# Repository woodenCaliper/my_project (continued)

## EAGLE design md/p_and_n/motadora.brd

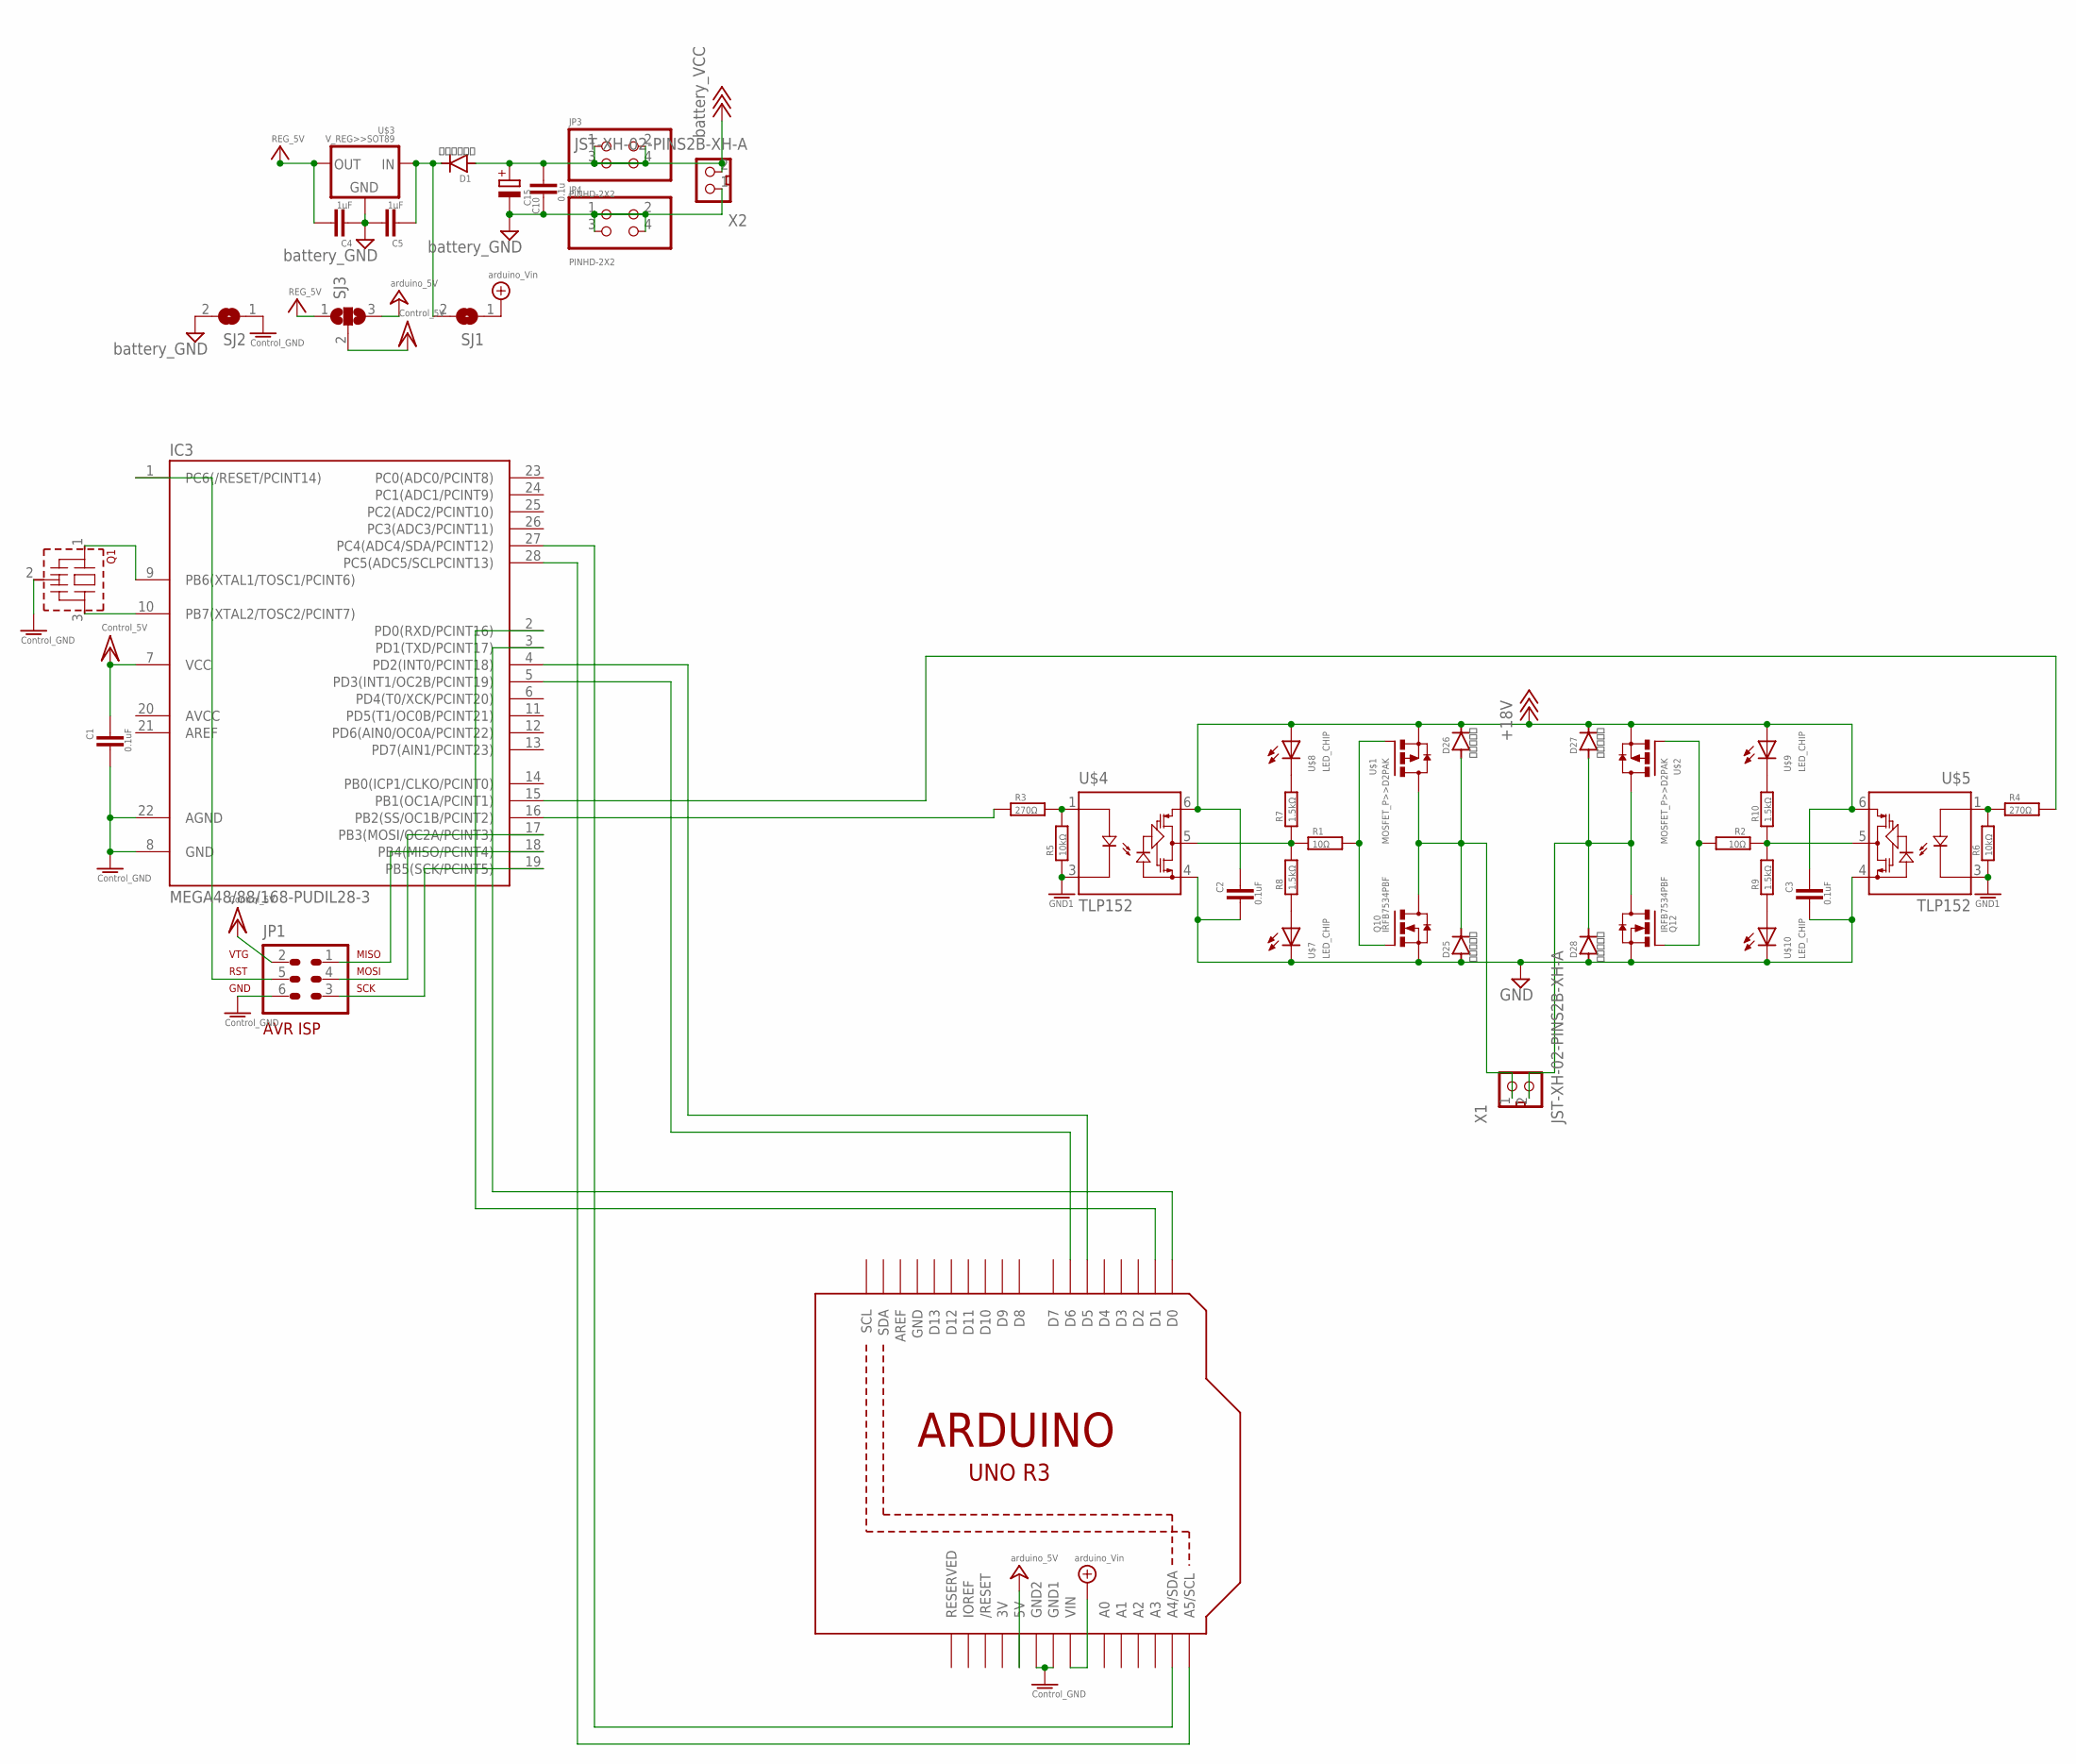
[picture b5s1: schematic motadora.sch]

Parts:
C1, C2, C3: 0.1uF; 2012
C4, C5: 1μF; C2012
C10: 0.1u; C025-025X050
C15: CPOL-EUTT2D5L; TT2D5L
D1: ＳＤ１０３Ａ; D-7.5
D25, D26, D27, D28: ＭＳ１８Ｆ; MS18F
IC3: MEGA48/88/168-PUDIL28-3; DIL28-3
JP1: AVR-ISP-6
JP3, JP4: PINHD-2X2; 2X02
Q1: CSTLS_G; CSTLS_G8
Q10, Q12: IRFB7534PBF; D2PACK
R1, R2: 10Ω; 2012
R3, R4: 270Ω; 2012
R5, R6: 10kΩ; 2012
R7, R8, R9, R10: 1.5kΩ; 2012
SJ1, SJ2: SJ
SJ3: SJ2W; SJ_2
U1: ARDUINOR3-BPLACE
U$1, U$2: MOSFET_P>>D2PAK; D2PAK
U$3: V_REG>>SOT89; SOT89
U$4, U$5: TLP152; 11-4L1S
U$7, U$8, U$9, U$10: LED_CHIP; 2012
X1, X2: JST-XH-02-PINS2B-XH-A; S2B-XH-A

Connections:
3V: U1.3V
+5V: C4.1, SJ3.1, U$3.1 (OUT)
+18V: C2.2, C3.2, C10.1, C15.+, D1.A, D26.P$2 (C), D27.P$2 (C), JP3.1, JP3.2, JP3.3, JP3.4, U$1.3 (S), U$2.3 (S), U$4.6, U$5.6, U$8.P$1 (A), U$9.P$1 (A), X2.2
GND: C2.1, C3.1, C4.2, C5.1, C10.2, C15.-, D25.P$1 (A), D28.P$1 (A), JP4.1, JP4.2, JP4.3, JP4.4, Q10.3 (S), Q12.3 (S), SJ2.2, U1.GND, U$3.2 (GND), U$3.2.1 (GND), U$4.4, U$5.4, U$7.P$2 (C), U$10.P$2 (C), X2.1
GND1: C1.1, IC3.8 (GND), IC3.22 (AGND), JP1.6, Q1.2 (VSS), R5.1, R6.1, SJ2.1, U1.GND1, U1.GND2, U$4.3, U$5.3
unnamed: R2.1, R9.2, R10.1, U$5.5
unnamed: Q12.1 (G), R2.2, U$2.1 (G)
unnamed: IC3.28 (PC5(ADC5/SCLPCINT13)), U1.A5 (A5/SCL)
unnamed: R3.2, R5.2, U$4.1
unnamed: R1.1, R7.1, R8.2, U$4.5
unnamed: R4.1, R6.2, U$5.1
unnamed: IC3.17 (PB3(MOSI/OC2A/PCINT3)), JP1.4
unnamed: IC3.27 (PC4(ADC4/SDA/PCINT12)), U1.A4 (A4/SDA)
unnamed: IC3.10 (PB7(XTAL2/TOSC2/PCINT7)), Q1.3
unnamed: IC3.3 (PD1(TXD/PCINT17)), U1.D0
unnamed: IC3.2 (PD0(RXD/PCINT16)), U1.D1
unnamed: C5.2, D1.C, SJ1.2, U$3.3 (IN)
unnamed: D25.P$2 (C), D26.P$1 (A), Q10.2 (D), U$1.4 (D), X1.1
unnamed: R7.2, U$8.P$2 (C)
unnamed: IC3.9 (PB6(XTAL1/TOSC1/PCINT6)), Q1.1
unnamed: R8.1, U$7.P$1 (A)
unnamed: IC3.1 (PC6(/RESET/PCINT14)), JP1.5
unnamed: Q10.1 (G), R1.2, U$1.1 (G)
unnamed: R9.1, U$10.P$1 (A)
unnamed: R10.2, U$9.P$2 (C)
unnamed: D27.P$1 (A), D28.P$2 (C), Q12.2 (D), U$2.4 (D), X1.2
unnamed: IC3.19 (PB5(SCK/PCINT5)), JP1.3
unnamed: IC3.4 (PD2(INT0/PCINT18)), U1.D5
unnamed: IC3.5 (PD3(INT1/OC2B/PCINT19)), U1.D6
unnamed: IC3.18 (PB4(MISO/PCINT4)), JP1.1
unnamed: IC3.16 (PB2(SS/OC1B/PCINT2)), R3.1
unnamed: IC3.15 (PB1(OC1A/PCINT1)), R4.2
VCC5: SJ3.3, U1.5V
VCC6: SJ1.1, U1.VIN
VCC7: C1.2, IC3.7 (VCC), JP1.2, SJ3.2

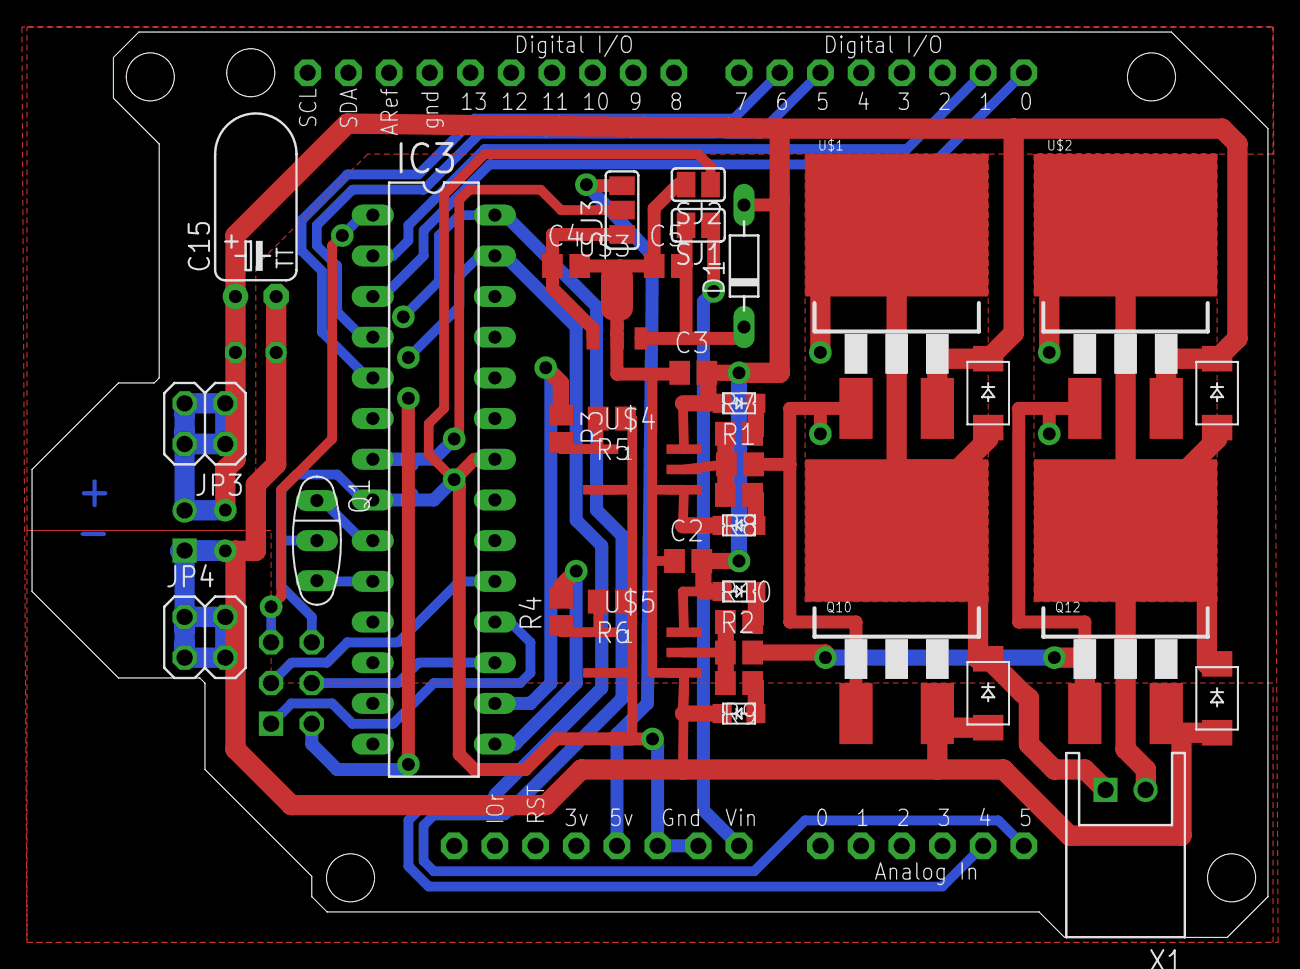
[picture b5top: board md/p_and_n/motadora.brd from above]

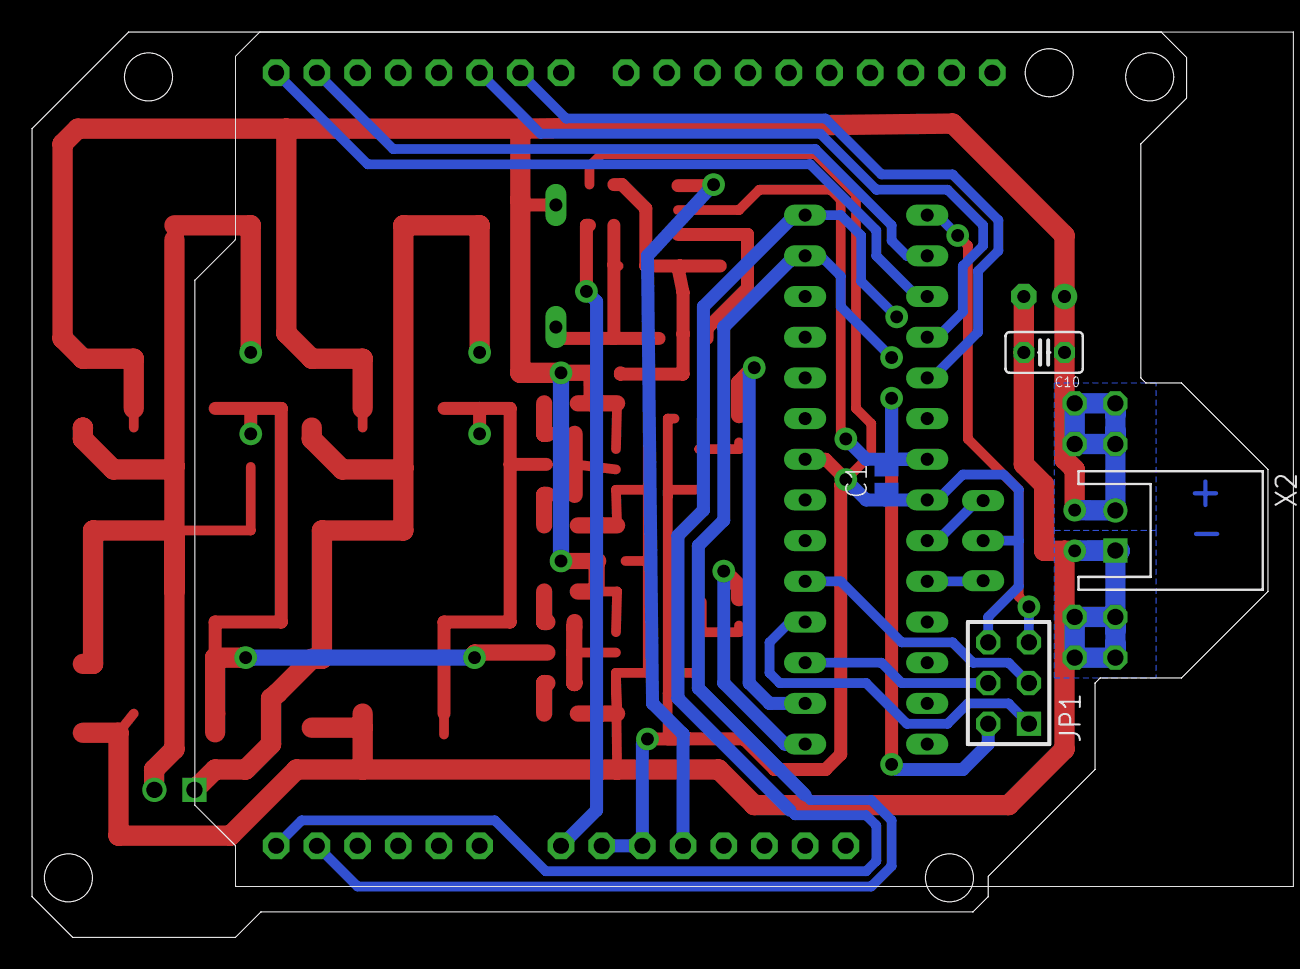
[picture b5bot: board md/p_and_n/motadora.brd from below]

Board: 2 copper layers, 77.2 x 56.5 mm, 44 parts (4 on the bottom side), 34 nets.

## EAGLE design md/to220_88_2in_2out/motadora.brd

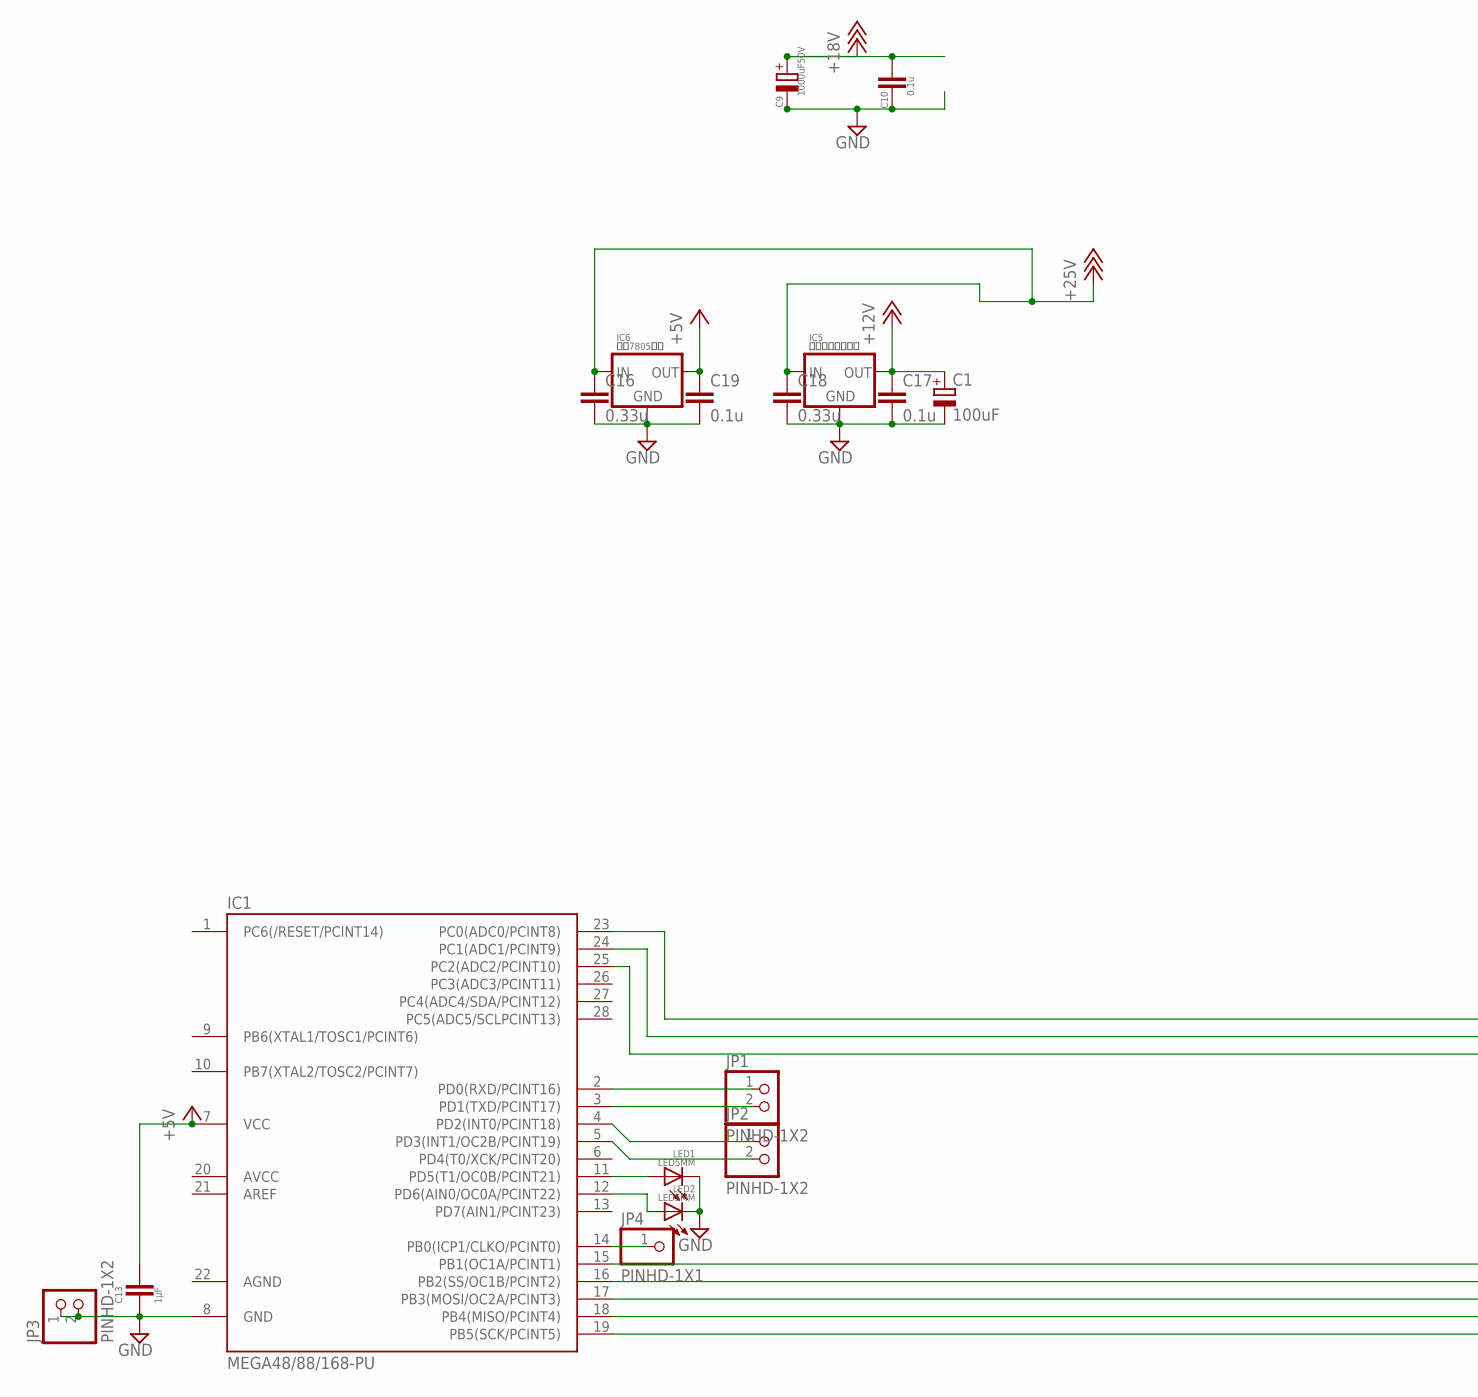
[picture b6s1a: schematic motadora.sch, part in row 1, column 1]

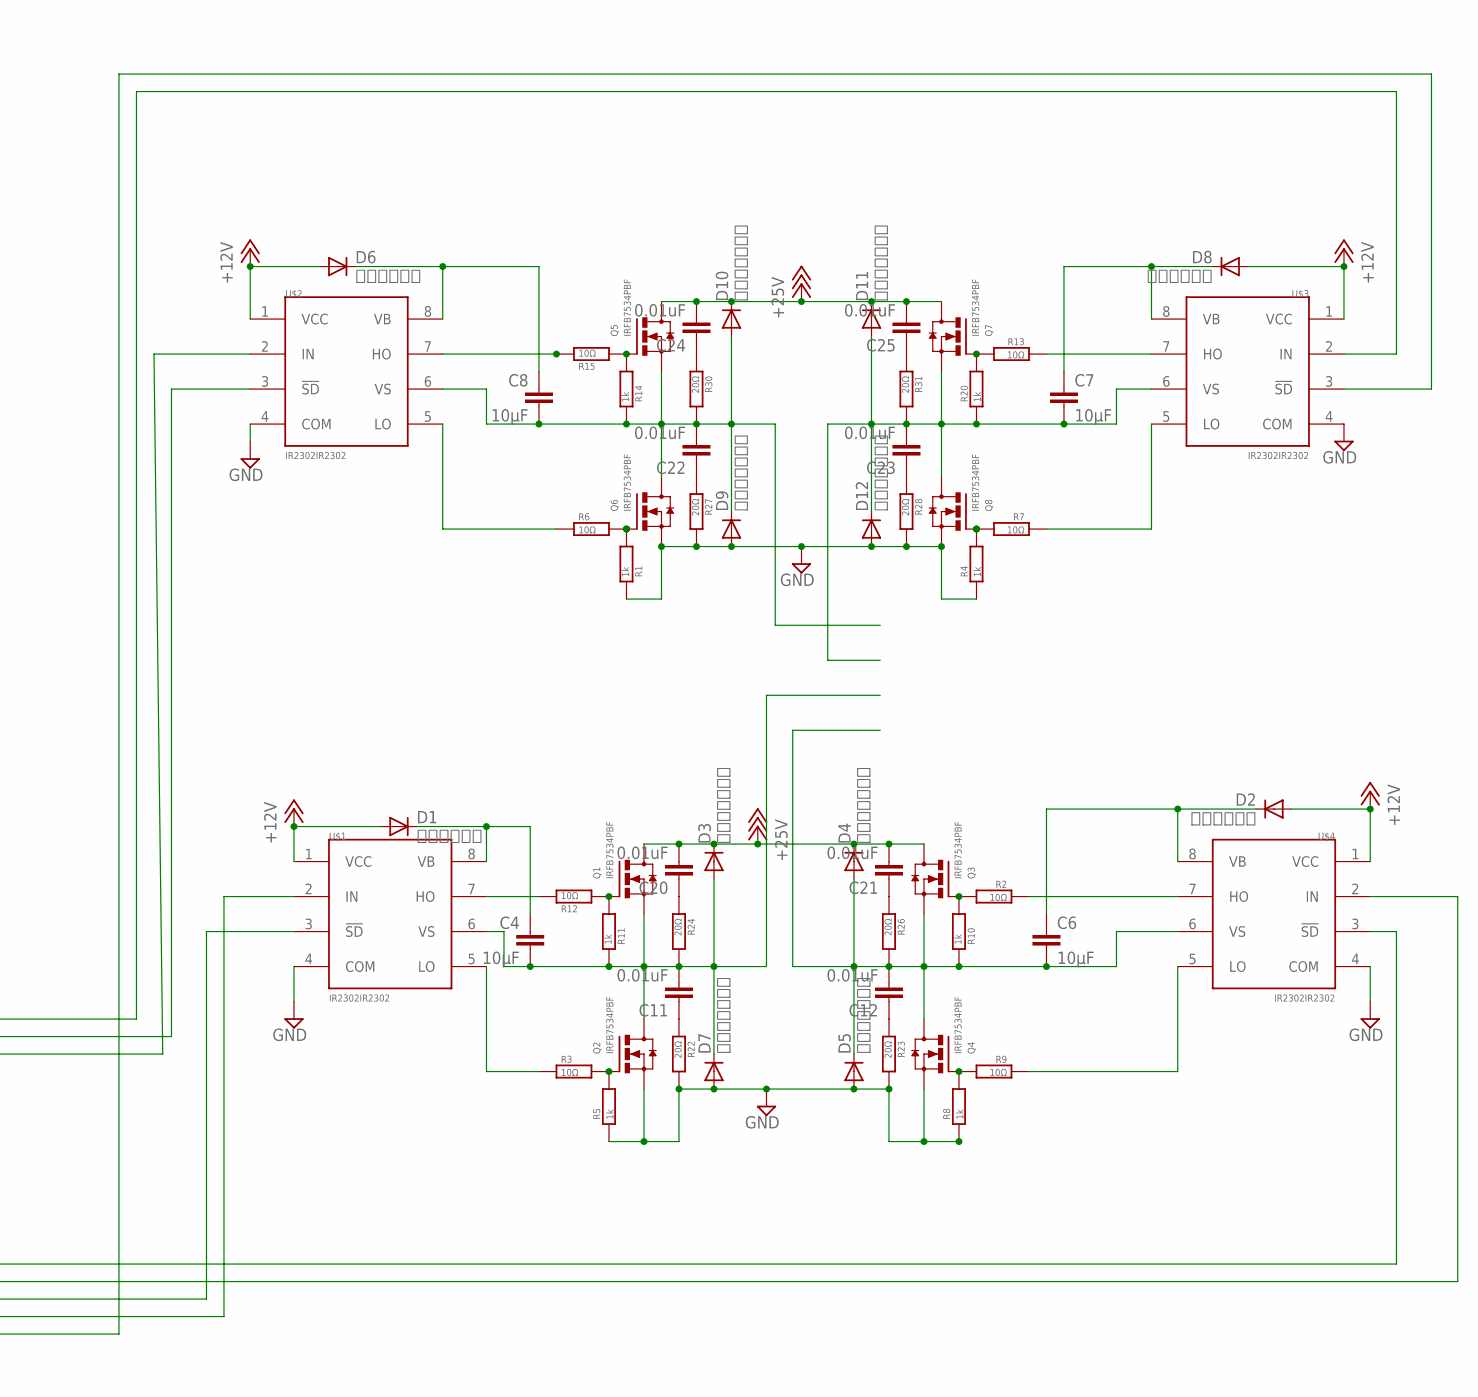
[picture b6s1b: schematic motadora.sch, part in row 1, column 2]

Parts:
C1: 100uF; TT2D6
C4, C6, C7, C8: 10μF; C025-025X050
C9: 1000uF50V; E2,5-7
C10, C17, C19: 0.1u; C025-025X050
C11, C12, C20, C21, C22, C23, C24, C25: 0.01uF; C025-024X044
C13: 1μF; C025-025X050
C16, C18: 0.33u; C025-025X050
D1, D2, D6, D8: ＳＤ１０３Ａ; D-5
D3, D4, D5, D7, D9, D10, D11, D12: １１ＥＱＳ０６; D-5
IC1: MEGA48/88/168-PU; DIL28-3
IC5: ＬＭ７８１２ＣＶ; TO-92
IC6: ＬＭ7805ＣＶ; TO-92
JP1, JP2, JP3: PINHD-1X2; 1X02
JP4: PINHD-1X1; 1X01
LED1, LED2: LED5MM
Q1, Q2, Q3, Q4, Q5, Q6, Q7, Q8: IRFB7534PBF; TO220_2
R1, R4, R5, R8, R10, R11, R14, R20: 1k; 1/4W(8MM)
R2, R3, R6, R7, R9, R12, R13, R15: 10Ω; 1/4W(2.5MM)_
R22, R23, R24, R26, R27, R28, R30, R31: 20Ω; 1/4W(2.5MM)_
U$1, U$2, U$3, U$4: IR2302IR2302; DIL08

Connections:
+5V: C13.1, C19.1, IC1.7 (VCC), IC6.1 (OUT)
+12V: C1.+, C17.1, D1.A, D2.A, D6.A, D8.A, IC5.1 (OUT), U$1.1 (VCC), U$2.1 (VCC), U$3.1 (VCC), U$4.1 (VCC)
+18V: C9.+, C10.1, C16.1, C18.1, C20.2, C21.2, C24.2, C25.2, D3.C, D4.C, D10.C, D11.C, IC5.3 (IN), IC6.3 (IN), Q1.2 (D), Q3.2 (D), Q5.2 (D), Q7.2 (D)
AGND: IC1.22 (AGND)
GND: C1.-, C9.-, C10.2, C13.2, C16.2, C17.2, C18.2, C19.2, D5.A, D7.A, D9.A, D12.A, IC1.8 (GND), IC5.2 (GND), IC6.2 (GND), JP3.1, JP3.2, LED1.K (C), LED2.K (C), Q2.3 (S), Q4.3 (S), Q6.3 (S), Q8.3 (S), R1.1, R4.1, R5.1, R8.1, R22.4 (2), R23.4 (2), R27.4 (2), R28.4 (2), U$1.4 (COM), U$2.4 (COM), U$3.4 (COM), U$4.4 (COM)
unnamed: R15.3 (1), U$2.7 (HO)
unnamed: R13.3 (1), U$3.7 (HO)
unnamed: R12.3 (1), U$1.7 (HO)
unnamed: Q2.1 (G), R3.4 (2), R5.2
unnamed: R2.3 (1), U$4.7 (HO)
unnamed: R6.3 (1), U$2.5 (LO)
unnamed: Q1.1 (G), R11.2, R12.4 (2)
unnamed: C4.2, C11.2, D3.A, D7.C, Q1.3 (S), Q2.2 (D), R11.1, R24.4 (2), U$1.6 (VS)
unnamed: C4.1, D1.C, U$1.8 (VB)
unnamed: C6.1, D2.C, U$4.8 (VB)
unnamed: R3.3 (1), U$1.5 (LO)
unnamed: C7.1, D8.C, U$3.8 (VB)
unnamed: Q5.1 (G), R14.2, R15.4 (2)
unnamed: C6.2, C12.2, D4.A, D5.C, Q3.3 (S), Q4.2 (D), R10.1, R26.4 (2), U$4.6 (VS)
unnamed: C8.1, D6.C, U$2.8 (VB)
unnamed: Q4.1 (G), R8.2, R9.4 (2)
unnamed: IC1.11 (PD5(T1/OC0B/PCINT21)), LED1.A
unnamed: C7.2, C23.2, D11.A, D12.C, Q7.3 (S), Q8.2 (D), R20.1, R31.4 (2), U$3.6 (VS)
unnamed: IC1.17 (PB3(MOSI/OC2A/PCINT3)), U$1.3 (!SD)
unnamed: Q6.1 (G), R1.2, R6.4 (2)
unnamed: IC1.15 (PB1(OC1A/PCINT1)), U$4.3 (!SD)
unnamed: IC1.12 (PD6(AIN0/OC0A/PCINT22)), LED2.A
unnamed: IC1.24 (PC1(ADC1/PCINT9)), U$2.3 (!SD)
unnamed: IC1.2 (PD0(RXD/PCINT16)), JP1.1
unnamed: Q8.1 (G), R4.2, R7.4 (2)
unnamed: C8.2, C22.2, D9.C, D10.A, Q5.3 (S), Q6.2 (D), R14.1, R30.4 (2), U$2.6 (VS)
unnamed: IC1.16 (PB2(SS/OC1B/PCINT2)), U$4.2 (IN)
unnamed: IC1.3 (PD1(TXD/PCINT17)), JP1.2
unnamed: IC1.4 (PD2(INT0/PCINT18)), JP2.1
unnamed: C12.1, R23.3 (1)
unnamed: IC1.5 (PD3(INT1/OC2B/PCINT19)), JP2.2
unnamed: C11.1, R22.3 (1)
unnamed: Q3.1 (G), R2.4 (2), R10.2
unnamed: R7.3 (1), U$3.5 (LO)
unnamed: IC1.23 (PC0(ADC0/PCINT8)), U$3.2 (IN)
unnamed: C20.1, R24.3 (1)
unnamed: C21.1, R26.3 (1)
unnamed: C22.1, R27.3 (1)
unnamed: C23.1, R28.3 (1)
unnamed: C24.1, R30.3 (1)
unnamed: C25.1, R31.3 (1)
unnamed: IC1.19 (PB5(SCK/PCINT5)), U$3.3 (!SD)
unnamed: IC1.18 (PB4(MISO/PCINT4)), U$1.2 (IN)
unnamed: Q7.1 (G), R13.4 (2), R20.2
unnamed: IC1.25 (PC2(ADC2/PCINT10)), U$2.2 (IN)
unnamed: IC1.14 (PB0(ICP1/CLKO/PCINT0)), JP4.1
unnamed: R9.3 (1), U$4.5 (LO)

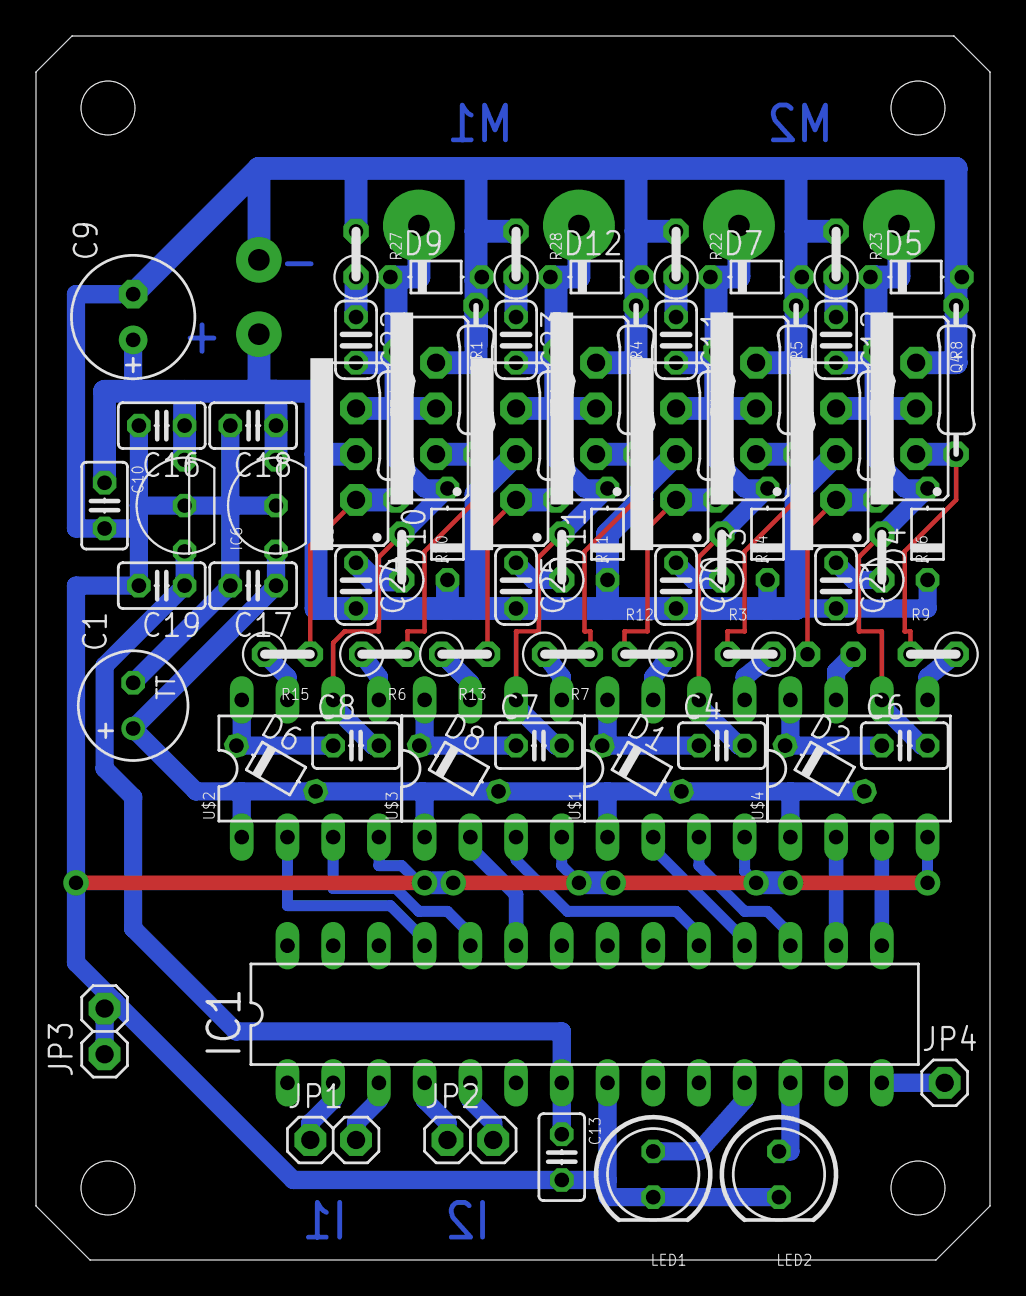
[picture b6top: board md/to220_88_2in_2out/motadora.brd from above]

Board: 2 copper layers, 53.0 x 68.0 mm, 77 parts (1 on the bottom side), 51 nets.

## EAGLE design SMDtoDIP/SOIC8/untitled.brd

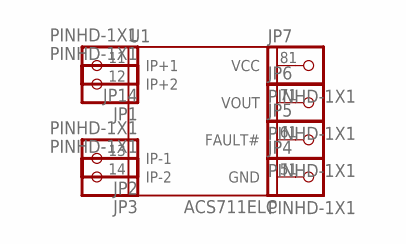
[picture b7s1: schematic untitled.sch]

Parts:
JP1, JP2, JP3, JP4, JP5, JP6, JP7, JP14: PINHD-1X1; 1X01
U1: ACS711ELC; SOIC8

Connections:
unnamed: JP14.1, U1.1 (IP+1)
unnamed: JP1.1, U1.2 (IP+2)
unnamed: JP2.1, U1.3 (IP-1)
unnamed: JP3.1, U1.4 (IP-2)
unnamed: JP4.1, U1.5 (GND)
unnamed: JP5.1, U1.6 (FAULT#)
unnamed: JP6.1, U1.7 (VOUT)
unnamed: JP7.1, U1.8 (VCC)

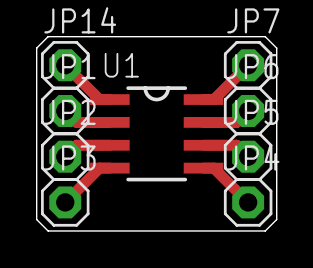
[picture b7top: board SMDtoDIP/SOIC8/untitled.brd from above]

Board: 2 copper layers, 13.3 x 10.8 mm, 9 parts (0 on the bottom side), 8 nets.

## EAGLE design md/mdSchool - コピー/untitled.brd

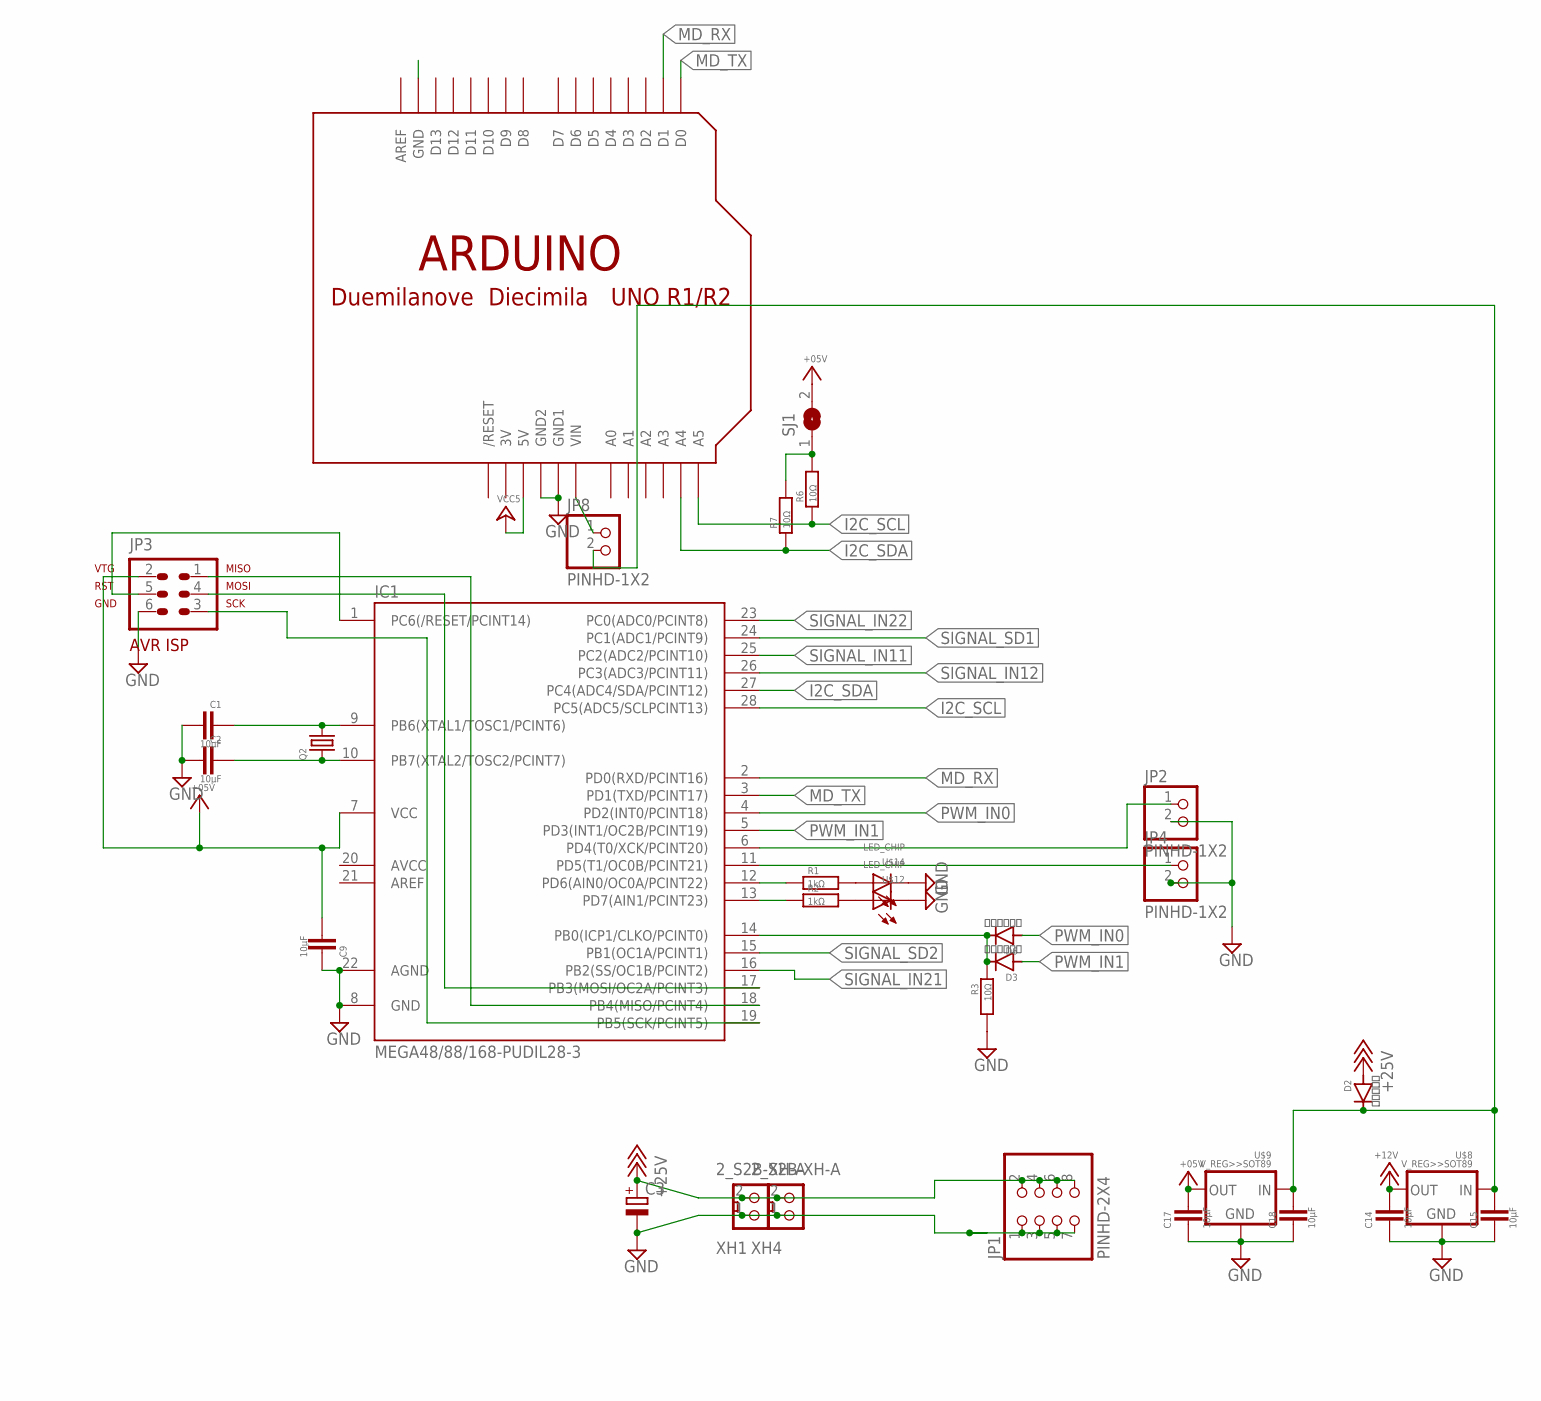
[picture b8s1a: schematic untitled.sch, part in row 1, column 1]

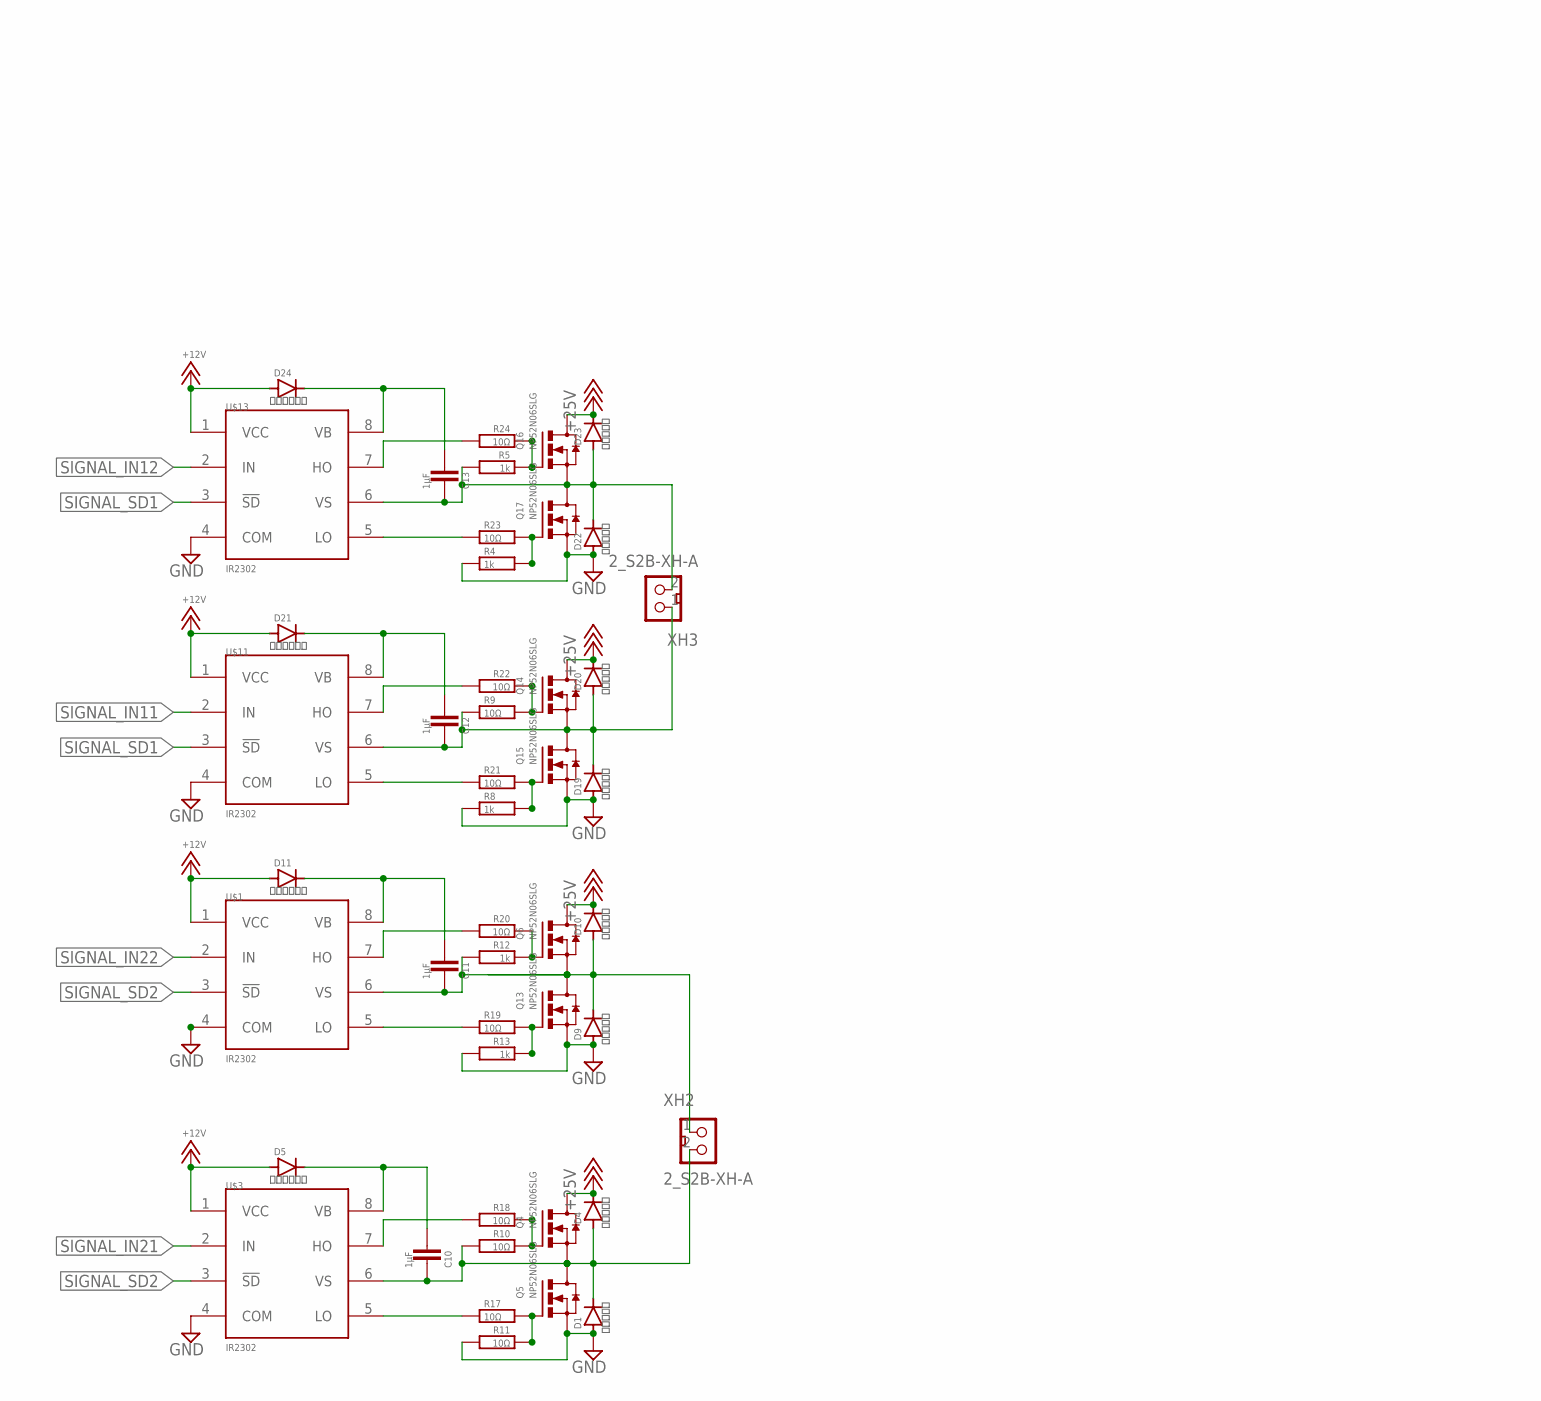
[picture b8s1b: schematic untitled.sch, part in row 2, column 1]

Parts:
C1, C2, C9, C14, C15, C17, C18: 10μF; 2012
C3: CPOL-EUUD-6,3X8,8; UD-6,3X5,8_NICHICON
C10, C11, C12, C13: 1μF; 2012
D1, D2, D4, D9, D10, D19, D20, D22, D23: ＭＳ１８Ｆ; MS18F
D3, D5, D6, D11, D21, D24: ＳＤ１０３Ａ; SOD123
IC1: MEGA48/88/168-PUDIL28-3; DIL28-3
JP1: PINHD-2X4; 2X04
JP2, JP4, JP8: PINHD-1X2; 1X02
JP3: AVR-ISP-6
Q2: CRYSTALHC49UP; HC49UP
Q4, Q5, Q6, Q13, Q14, Q15, Q16, Q17: NP52N06SLG; TO252
R1, R2: 1kΩ; 2012
R3, R6, R7, R9, R10, R11, R17, R18, R19, R20, R21, R22, R23, R24: 10Ω; 2012
R4, R5, R8, R12, R13: 1k; 2012
SJ1: SJ
U$1, U$3, U$11, U$13: IR2302; DIL08
U$2: ARDUINO-NOHOLE
U$8, U$9: V_REG>>SOT89; SOT89
U$12, U$14: LED_CHIP; 2012
XH1, XH2, XH3, XH4: 2_S2B-XH-A; S2B-XH-A

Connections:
3V: U$2.3V
+5V: C9.1, C17.1, IC1.7 (VCC), JP3.2, SJ1.2, U$9.1 (OUT)
+12V: C14.1, D5.A, D11.A, D21.A, D24.A, U$1.1 (VCC), U$3.1 (VCC), U$8.1 (OUT), U$11.1 (VCC), U$13.1 (VCC)
+18V: C3.+, D2.P$1 (A), D4.P$2 (C), D10.P$2 (C), D20.P$2 (C), D23.P$2 (C), JP1.2, JP1.4, JP1.6, JP1.8, Q4.3 (D), Q6.3 (D), Q14.3 (D), Q16.3 (D), XH1.2, XH4.2
GND: C1.1, C2.1, C3.-, C9.2, C14.2, C15.2, C17.2, C18.2, D1.P$1 (A), D9.P$1 (A), D19.P$1 (A), D22.P$1 (A), IC1.8 (GND), IC1.22 (AGND), JP1.1, JP1.3, JP1.5, JP1.7, JP2.2, JP3.6, JP4.2, Q5.2 (S), Q13.2 (S), Q15.2 (S), Q17.2 (S), R3.2, R4.1, R8.1, R11.2, R13.2, U$1.4 (COM), U$2.GND1, U$2.GND2, U$3.4 (COM), U$8.2 (GND), U$8.2.1 (GND), U$9.2 (GND), U$9.2.1 (GND), U$11.4 (COM), U$12.P$2 (C), U$13.4 (COM), U$14.P$2 (C), XH1.1, XH4.1
I2C_SCL: IC1.28 (PC5(ADC5/SCLPCINT13)), R6.1, U$2.A5
I2C_SDA: IC1.27 (PC4(ADC4/SDA/PCINT12)), R7.1, U$2.A4
MD_RX: IC1.2 (PD0(RXD/PCINT16)), U$2.D1
MD_TX: IC1.3 (PD1(TXD/PCINT17)), U$2.D0
unnamed: C15.1, C18.1, D2.P$2 (C), JP8.2, U$8.3 (IN), U$9.3 (IN)
unnamed: JP8.1, U$2.VIN
unnamed: C13.2, D22.P$2 (C), D23.P$1 (A), Q16.2 (S), Q17.3 (D), R5.2, U$13.6 (VS), XH3.2
unnamed: D3.C, D6.C, IC1.14 (PB0(ICP1/CLKO/PCINT0)), R3.1
unnamed: IC1.1 (PC6(/RESET/PCINT14)), JP3.5
unnamed: IC1.12 (PD6(AIN0/OC0A/PCINT22)), R1.1
unnamed: C1.2, IC1.9 (PB6(XTAL1/TOSC1/PCINT6)), Q2.2
unnamed: C2.2, IC1.10 (PB7(XTAL2/TOSC2/PCINT7)), Q2.1
unnamed: IC1.11 (PD5(T1/OC0B/PCINT21)), JP4.1
unnamed: IC1.13 (PD7(AIN1/PCINT23)), R2.1
unnamed: IC1.19 (PB5(SCK/PCINT5)), JP3.3
unnamed: C11.2, D9.P$2 (C), D10.P$1 (A), Q6.2 (S), Q13.3 (D), R12.2, U$1.6 (VS), XH2.1
unnamed: IC1.6 (PD4(T0/XCK/PCINT20)), JP2.1
unnamed: R1.2, U$14.P$1 (A)
unnamed: R2.2, U$12.P$1 (A)
unnamed: C10.2, D1.P$2 (C), D4.P$1 (A), Q4.2 (S), Q5.3 (D), R10.2, U$3.6 (VS), XH2.2
unnamed: Q5.1 (G), R11.1, R17.2
unnamed: R17.1, U$3.5 (LO)
unnamed: R6.2, R7.2, SJ1.1
unnamed: IC1.17 (PB3(MOSI/OC2A/PCINT3)), JP3.4
unnamed: IC1.18 (PB4(MISO/PCINT4)), JP3.1
unnamed: R18.2, U$3.7 (HO)
unnamed: C10.1, D5.C, U$3.8 (VB)
unnamed: Q4.1 (G), R10.1, R18.1
unnamed: Q13.1 (G), R13.1, R19.2
unnamed: R19.1, U$1.5 (LO)
unnamed: R20.2, U$1.7 (HO)
unnamed: C11.1, D11.C, U$1.8 (VB)
unnamed: Q6.1 (G), R12.1, R20.1
unnamed: C12.2, D19.P$2 (C), D20.P$1 (A), Q14.2 (S), Q15.3 (D), R9.1, U$11.6 (VS), XH3.1
unnamed: Q15.1 (G), R8.2, R21.2
unnamed: R21.1, U$11.5 (LO)
unnamed: R22.2, U$11.7 (HO)
unnamed: C12.1, D21.C, U$11.8 (VB)
unnamed: Q14.1 (G), R9.2, R22.1
unnamed: Q17.1 (G), R4.2, R23.2
unnamed: R23.1, U$13.5 (LO)
unnamed: R24.2, U$13.7 (HO)
unnamed: C13.1, D24.C, U$13.8 (VB)
unnamed: Q16.1 (G), R5.1, R24.1
PWM_IN0: D6.A, IC1.4 (PD2(INT0/PCINT18))
PWM_IN1: D3.A, IC1.5 (PD3(INT1/OC2B/PCINT19))
SIGNAL_IN11: IC1.25 (PC2(ADC2/PCINT10)), U$11.2 (IN)
SIGNAL_IN12: IC1.26 (PC3(ADC3/PCINT11)), U$13.2 (IN)
SIGNAL_IN21: IC1.16 (PB2(SS/OC1B/PCINT2)), U$3.2 (IN)
SIGNAL_IN22: IC1.23 (PC0(ADC0/PCINT8)), U$1.2 (IN)
SIGNAL_SD1: IC1.24 (PC1(ADC1/PCINT9)), U$11.3 (!SD), U$13.3 (!SD)
SIGNAL_SD2: IC1.15 (PB1(OC1A/PCINT1)), U$1.3 (!SD), U$3.3 (!SD)
VCC5: U$2.5V
